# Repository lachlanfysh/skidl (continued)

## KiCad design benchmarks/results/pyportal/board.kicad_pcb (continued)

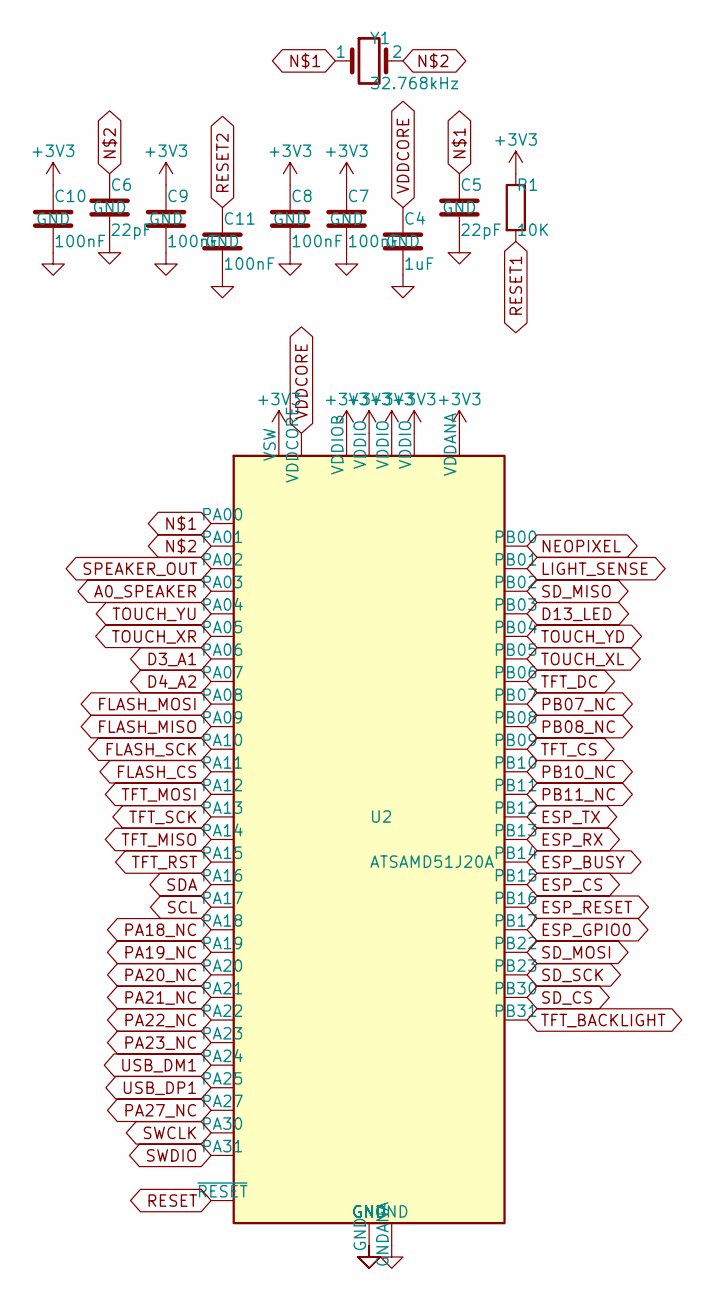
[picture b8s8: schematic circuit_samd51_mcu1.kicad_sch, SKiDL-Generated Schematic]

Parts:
C4: 1uF; C_0603_1608Metric
C5, C6: 22pF; C_0402_1005Metric
C7, C8, C9, C10: 100nF; C_0603_1608Metric
C11: 100nF; C_0402_1005Metric
R1: 10K; R_0402_1005Metric
U2: ATSAMD51J20A; LQFP-64_10x10mm_P0.5mm
Y1: 32.768kHz; Crystal_SMD_3215-2Pin_3.2x1.5mm

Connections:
+3V3: C7.1, C8.1, C9.1, C10.1, R1.1, U2.8 (VDDANA), U2.21 (VDDIOB), U2.34 (VDDIO), U2.48 (VDDIO), U2.55 (VSW), U2.56 (VDDIO); also elsewhere on the board
A0_SPEAKER: U2.4 (PA03)
D3_A1: U2.15 (PA06)
D4_A2: U2.16 (PA07)
D13_LED: U2.64 (PB03)
ESP_BUSY: U2.27 (PB14)
ESP_CS: U2.28 (PB15)
ESP_GPIO0: U2.40 (PB17)
ESP_RESET: U2.39 (PB16)
ESP_RX: U2.26 (PB13)
ESP_TX: U2.25 (PB12)
FLASH_CS: U2.20 (PA11)
FLASH_MISO: U2.18 (PA09)
FLASH_MOSI: U2.17 (PA08)
FLASH_SCK: U2.19 (PA10)
GND: C4.2, C5.2, C6.2, C7.2, C8.2, C9.2, C10.2, C11.2, U2.7 (GNDANA), U2.22 (GND), U2.33 (GND), U2.47 (GND), U2.54 (GND); also elsewhere on the board
LIGHT_SENSE: U2.62 (PB01)
unnamed: C5.1, U2.1 (PA00), Y1.1
unnamed: C6.1, U2.2 (PA01), Y1.2
NEOPIXEL: U2.61 (PB00)
PA18_NC: U2.37 (PA18)
PA19_NC: U2.38 (PA19)
PA20_NC: U2.41 (PA20)
PA21_NC: U2.42 (PA21)
PA22_NC: U2.43 (PA22)
PA23_NC: U2.44 (PA23)
PA27_NC: U2.51 (PA27)
PB07_NC: U2.10 (PB07)
PB08_NC: U2.11 (PB08)
PB10_NC: U2.23 (PB10)
PB11_NC: U2.24 (PB11)
RESET: U2.52 (~RESET)
RESET1: R1.2
RESET2: C11.1
SCL: U2.36 (PA17)
SDA: U2.35 (PA16)
SD_CS: U2.59 (PB30)
SD_MISO: U2.63 (PB02)
SD_MOSI: U2.49 (PB22)
SD_SCK: U2.50 (PB23)
SPEAKER_OUT: U2.3 (PA02)
SWCLK: U2.57 (PA30)
SWDIO: U2.58 (PA31)
TFT_BACKLIGHT: U2.60 (PB31)
TFT_CS: U2.12 (PB09)
TFT_DC: U2.9 (PB06)
TFT_MISO: U2.31 (PA14)
TFT_MOSI: U2.29 (PA12)
TFT_RST: U2.32 (PA15)
TFT_SCK: U2.30 (PA13)
TOUCH_XL: U2.6 (PB05)
TOUCH_XR: U2.14 (PA05)
TOUCH_YD: U2.5 (PB04)
TOUCH_YU: U2.13 (PA04)
USB_DM1: U2.45 (PA24)
USB_DP1: U2.46 (PA25)
VDDCORE: C4.1, U2.53 (VDDCORE)

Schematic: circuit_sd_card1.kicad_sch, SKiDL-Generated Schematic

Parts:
C17: 100nF; C_0603_1608Metric
J2: microSD; microSD_HC_Molex_104031-0811
R6, R7: 10K; R_0402_1005Metric

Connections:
+3V3: C17.1, J2.4 (VDD), R6.1, R7.1; also elsewhere on the board
GND: C17.2, J2.6 (VSS), J2.9 (SHIELD); also elsewhere on the board
unnamed: J2.8 (DAT1), R6.2
unnamed: J2.1 (DAT2), R7.2
SD_CS1: J2.2 (DAT3/CD)
SD_MISO1: J2.7 (DAT0)
SD_MOSI1: J2.3 (CMD)
SD_SCK1: J2.5 (CLK)

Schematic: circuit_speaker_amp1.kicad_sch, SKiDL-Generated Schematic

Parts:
C20: 1uF; C_0603_1608Metric
C21: 100nF; C_0603_1608Metric
C22: 10uF; C_0805_2012Metric
J3: Speaker; JST_PH_S2B-PH-K_1x02_P2.00mm_Horizontal
U8: PAM8302A; SOIC-8_3.9x4.9mm_P1.27mm

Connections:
+3V3: C21.1, C22.1, U8.1 (nSD), U8.6 (VDD); also elsewhere on the board
GND: C21.2, C22.2, U8.3 (INN), U8.4 (GND_AMP1), U8.7 (GND_AMP2); also elsewhere on the board
unnamed: C20.2, U8.2 (INP)
unnamed: J3.1, U8.5 (OUTP)
unnamed: J3.2, U8.8 (OUTN)
SPEAKER_OUT1: C20.1

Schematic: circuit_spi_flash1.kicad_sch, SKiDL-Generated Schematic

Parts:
C16: 100nF; C_0603_1608Metric
U5: W25Q64JV-8MB; SOIC-8_3.9x4.9mm_P1.27mm

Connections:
+3V3: C16.1, U5.3 (~WP/IO_{2}), U5.7 (~HOLD/~RESET/IO_{3}), U5.8 (VCC); also elsewhere on the board
FLASH_CS1: U5.1 (~CS)
FLASH_MISO1: U5.2 (DO/IO_{1})
FLASH_MOSI1: U5.5 (DI/IO_{0})
FLASH_SCK1: U5.6 (CLK)
GND: C16.2, U5.4 (GND); also elsewhere on the board

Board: 2 copper layers, 54 parts (0 on the bottom side), 16 nets, no tracks yet.

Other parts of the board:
C15, C18: 100nF; C_0603_1608Metric
Q1: 2N7002; SOT-23
R5: 10R; R_0603_1608Metric
U4: ILI9341_320x240; PinHeader_2x07_P2.54mm_Vertical
U6: ADT7410; SOIC-8_3.9x4.9mm_P1.27mm

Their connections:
+3V3: C15.1, C18.1, R5.1, U4.1, U6.8; also elsewhere on the board
GND: C15.2, C18.2, Q1.3, U4.2, U4.10, U6.3, U6.4, U6.7; also elsewhere on the board
unnamed: Q1.2, R5.2, U4.7

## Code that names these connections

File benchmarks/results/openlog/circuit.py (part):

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                  footprint="Capacitor_SMD:C_0402_1005Metric")
    c_aref[1] += mcu["AREF"]; c_aref[2] += gnd

    # Crystal pins (PB6/PB7 = XTAL1/XTAL2)
    mcu["XTAL1/PB6"] += xtal1
    mcu["XTAL2/PB7"] += xtal2

    # SPI → SD card (PB2=SS/SD_CS, PB3=MOSI, PB4=MISO, PB5=SCK)
    mcu["PB2"] += sd_cs
    mcu["PB3"] += spi_mosi
    mcu["PB4"] += spi_miso
    mcu["PB5"] += spi_sck

    # UART (PD0=RX, PD1=TX)
    mcu["PD0"] += uart_rx
    mcu["PD1"] += uart_tx

    # RESET pin with pull-up resistor
    mcu["~{RESET}/PC6"] += reset
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
@subcircuit
def ftdi_header_block(vcc, gnd, uart_rx, uart_tx, reset, dtr_reset):
    """FTDI-compatible 6-pin serial header (DTR/RX/TX/+5V/CTS/GND)."""
    hdr = Part(
        "Connector", "Conn_01x06_Pin",
        footprint="Connector_PinHeader_2.54mm:PinHeader_1x06_P2.54mm_Vertical",
        value="FTDI_HEADER",
    )
    # Standard FTDI header pinout: 1=DTR, 2=RX-in, 3=TX-out, 4=+5V, 5=CTS, 6=GND
    hdr["Pin_1"] += dtr_reset    # DTR → auto-reset circuit
    hdr["Pin_2"] += uart_rx      # FTDI TX → MCU RX
    hdr["Pin_3"] += uart_tx      # FTDI RX ← MCU TX
    hdr["Pin_4"] += vcc          # 5 V power from FTDI
    hdr["Pin_5"] += Net("CTS")   # CTS (tied high via resistor below)
    hdr["Pin_6"] += gnd

    # DTR auto-reset: 100nF coupling cap to RESET
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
